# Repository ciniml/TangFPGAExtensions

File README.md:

# Extension boards for Tang series FPGA boards.

## 概要

Sipeedが製造・販売している、Tang Nano 9K, Tang Nano 20K およびTang Primer 20K向けのベースボードおよび拡張基板の設計データです。

## 内容

### 対象ボード

| 名前            | 略称  | 説明                    | 購入先ページ                                              |
| :-------------- | :---- | :---------------------- | :-------------------------------------------------------- |
| Tang Nano 9K    | TN9K  | GW1NR-LV9搭載のボード。 | [秋月電子](https://akizukidenshi.com/catalog/g/gM-17448/) |
| Tang Primer 20K | TN20K | GW2A-LV18PG256          | [秋月電子](https://akizukidenshi.com/catalog/g/gM-17540/) |

### 基板一覧

| 名前                                                                        | 対象ボード | 説明                                            | KiCadプロジェクト                                                                  | リビジョン |
| :-------------------------------------------------------------------------- | :--------- | :---------------------------------------------- | :--------------------------------------------------------------------------------- | ---------- |
| [Tang Nano 9K Pmod Base Board](./README_TangNano_PmodBase.md)               | TN9K       | Tang Nano 9K用のPmod接続用ベースボード          | [TangNano_PmodBase.kicad_pro](./TangNano_PmodBase.kicad_pro)                       | Rev. B     |
| [Tang Primer 20K Pmod Extender ](./README_TangPrimer_PmodExtender.md)       | TP20K      | Tang Primer 20K用のPmod接続用拡張基板           | [TangPrimer_PmodExtender.kicad_pro](./TangPrimer_PmodExtender.kicad_pro)           | Rev. B     |
| [Pmod Debug Board](./README_Pmod_Debug.md)                                  | TN9K,TP20K | Pmodのデバッグ用中継基板                        | [Pmod_Debug.kicad_pro](./Pmod_Debug.kicad_pro)                                     | Rev. A     |
| Pmod HUB75 Connector Board                                                  | TN9K,TP20K | HUB75 LED Matrix接続用Pmod基板                  | [Pmod_HUB75.kicad_pro](./Pmod_HUB75.kicad_pro)                                     | Rev. A     |
| Pmod LED Board                                                              | TN9K,TP20K | Pmodのデバッグ用LED基板                         | [Pmod_LED.kicad_pro](./Pmod_LED.kicad_pro)                                         | Rev. A     |
| [Pmod Matrix LED](./README_Pmod_MatrixLED.md)                               | TN9K,TP20K | 8x8単色LEDマトリクスPmod基板                    | [Pmod_MatrixLED.kicad_pro](./Pmod_MatrixLED.kicad_pro)                             | Rev. B     |
| [Pmod MultiSegment (Single Port)](./README_Pmod_MultiSegment_SinglePort.md) | TN9K,TP20K | 6桁7+1セグメントLED Pmod基板 (シングルポート版) | [Pmod_MultiSegment_SinglePort.kicad_pro](./Pmod_MultiSegment_SinglePort.kicad_pro) | Rev. A     |
| [Pmod Adapter Ethernet](./README_Pmod_Adapter_Ethernet.md) | TN9K,TP20K | LAN8720 Ethernet PHYボード用 Pmod アダプタ | [Pmod_Adapter_Ethernet.kicad_pro](./Pmod_Adapter_Ethernet.kicad_pro) | Rev. A     |

## ライセンス

<br />この 作品 は <a rel="license" href="http://creativecommons.org/licenses/by/4.0/">クリエイティブ・コモンズ 表示 4.0 国際 ライセンス</a>の下に提供されています。

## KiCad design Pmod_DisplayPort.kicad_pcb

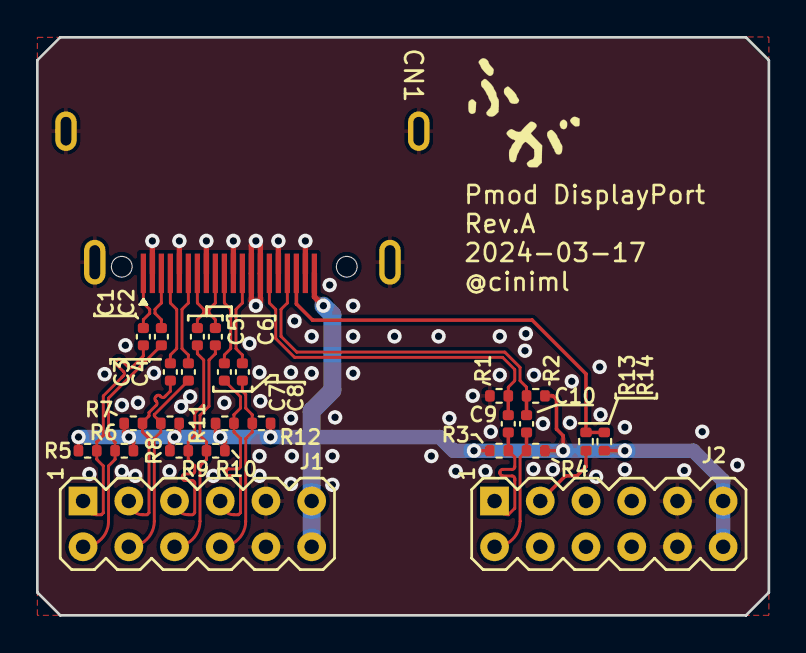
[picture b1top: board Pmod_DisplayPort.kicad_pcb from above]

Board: 2 copper layers, 40.6 x 32.1 mm, 28 parts (0 on the bottom side), 24 nets.

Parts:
C1, C2, C3, C4, C5, C6, C7, C8, C9, C10: 100n; C_0402_1005Metric
CN1: DisplayPort_DP-GD-120PWB
J1, J2: Conn_02x06_Top_Bottom; Conn_Pmod_Spec_B_Thin
LOGO1: Logo_Open_Hardware_Small; logo
R1, R2, R13: 100k; R_0402_1005Metric
R3, R4, R5, R6, R7, R8, R9, R10, R11, R12: 50; R_0402_1005Metric
R14: 10k; R_0402_1005Metric

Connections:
+3V3: CN1.20 (DP_PWR), J1.6, J1.12, J2.6, J2.12, R2.1, R3.1, R4.1, R5.1, R6.1, R7.1, R8.1, R9.1, R10.1, R11.1, R12.1, R13.1
/AUX_N: C10.2, CN1.17 (AUX_CH_N), R2.2
/AUX_P: C9.2, CN1.15 (AUX_CH_P), R1.2
/HPD: CN1.18 (HOT_PLUG), R13.2, R14.1
/ML0_N: C2.2, CN1.3 (ML_LANE0_N)
/ML0_P: C1.2, CN1.1 (ML_LANE0_P)
/ML1_N: C4.2, CN1.6 (ML_LANE1_N)
/ML1_P: C3.2, CN1.4 (ML_LANE1_P)
/ML2_N: C6.2, CN1.9 (ML_LANE2_N)
/ML2_P: C5.2, CN1.7 (ML_LANE2_P)
/ML3_N: C8.2, CN1.12 (ML_LANE3_N)
/ML3_P: C7.2, CN1.10 (ML_LANE3_P)
/PMOD_AUX_CH_N: C10.1, J2.7, R4.2
/PMOD_AUX_CH_P: C9.1, J2.1, R3.2
/PMOD_L0_N: C2.1, J1.7, R6.2
/PMOD_L0_P: C1.1, J1.1, R5.2
/PMOD_L1_N: C4.1, J1.8, R8.2
/PMOD_L1_P: C3.1, J1.2, R7.2
/PMOD_L2_N: C6.1, J1.9, R10.2
/PMOD_L2_P: C5.1, J1.3, R9.2
/PMOD_L3_N: C8.1, J1.10, R12.2
/PMOD_L3_P: C7.1, J1.4, R11.2
/PMOD_P2_HOT_PLUG: J2.2, R14.2
GND: CN1.2 (GND), CN1.5 (GND), CN1.8 (GND), CN1.11 (GND), CN1.13 (CONFIG1), CN1.14 (CONFIG2), CN1.16 (GND), CN1.19 (Return), CN1.FG, J1.5, J1.11, J2.5, J2.11, R1.1

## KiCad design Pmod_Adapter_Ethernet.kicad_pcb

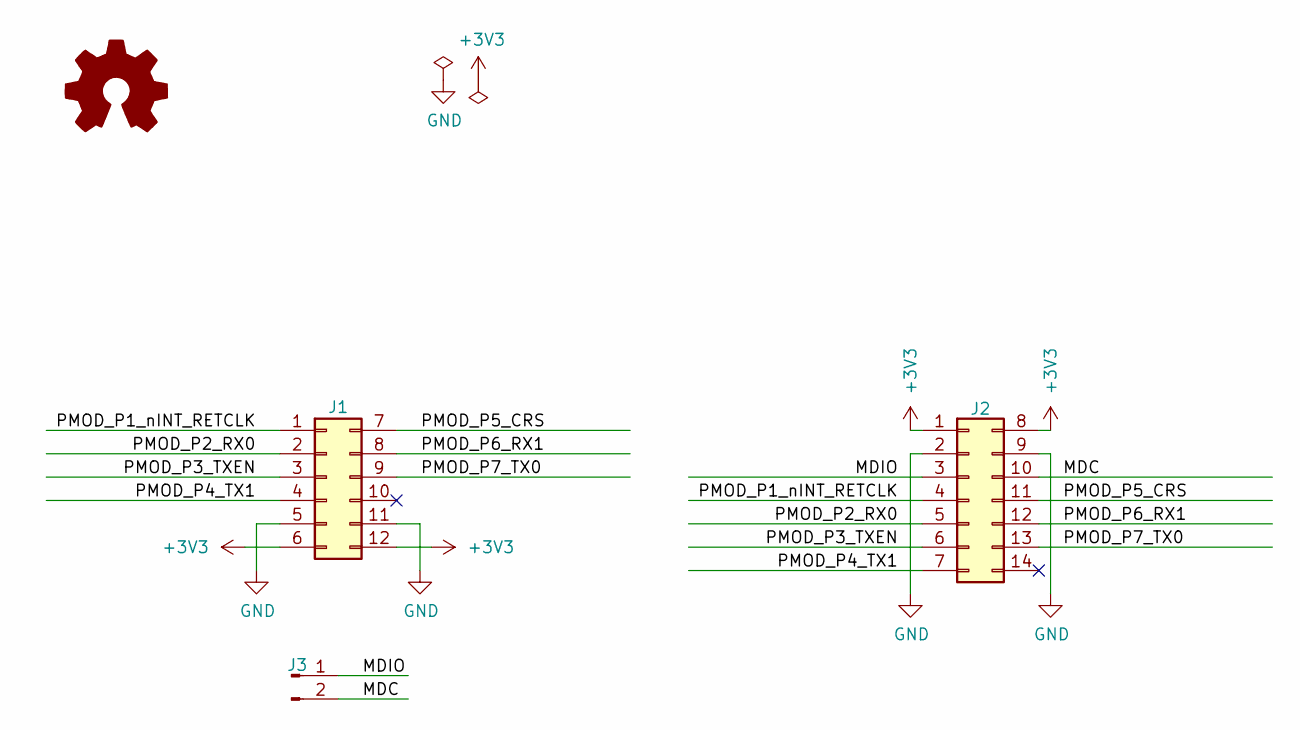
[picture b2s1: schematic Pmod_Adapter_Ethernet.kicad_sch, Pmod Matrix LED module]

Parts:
J1: Conn_02x06_Top_Bottom; Conn_Pmod_Spec_B_Thin
J2: Conn_02x07_Top_Bottom; Conn_WaveShare_Ethernet_Spec_D_Thin
J3: Conn_01x02_Pin; PinHeader_1x02_P2.54mm_Vertical
LOGO1: Logo_Open_Hardware_Small; logo

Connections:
+3V3: J1.6, J1.12, J2.1, J2.8
/MDC: J2.10, J3.2
/MDIO: J2.3, J3.1
/PMOD_P1_nINT_RETCLK: J1.1, J2.4
/PMOD_P2_RX0: J1.2, J2.5
/PMOD_P3_TXEN: J1.3, J2.6
/PMOD_P4_TX1: J1.4, J2.7
/PMOD_P5_CRS: J1.7, J2.11
/PMOD_P6_RX1: J1.8, J2.12
/PMOD_P7_TX0: J1.9, J2.13
GND: J1.5, J1.11, J2.2, J2.9

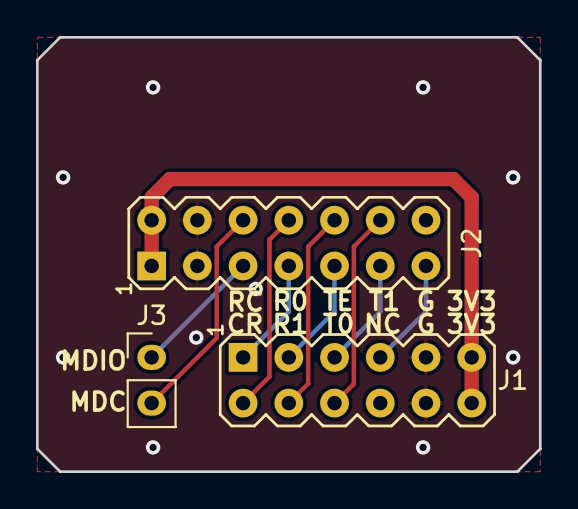
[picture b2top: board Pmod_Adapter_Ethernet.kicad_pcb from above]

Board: 2 copper layers, 27.9 x 24.1 mm, 4 parts (1 on the bottom side), 11 nets.

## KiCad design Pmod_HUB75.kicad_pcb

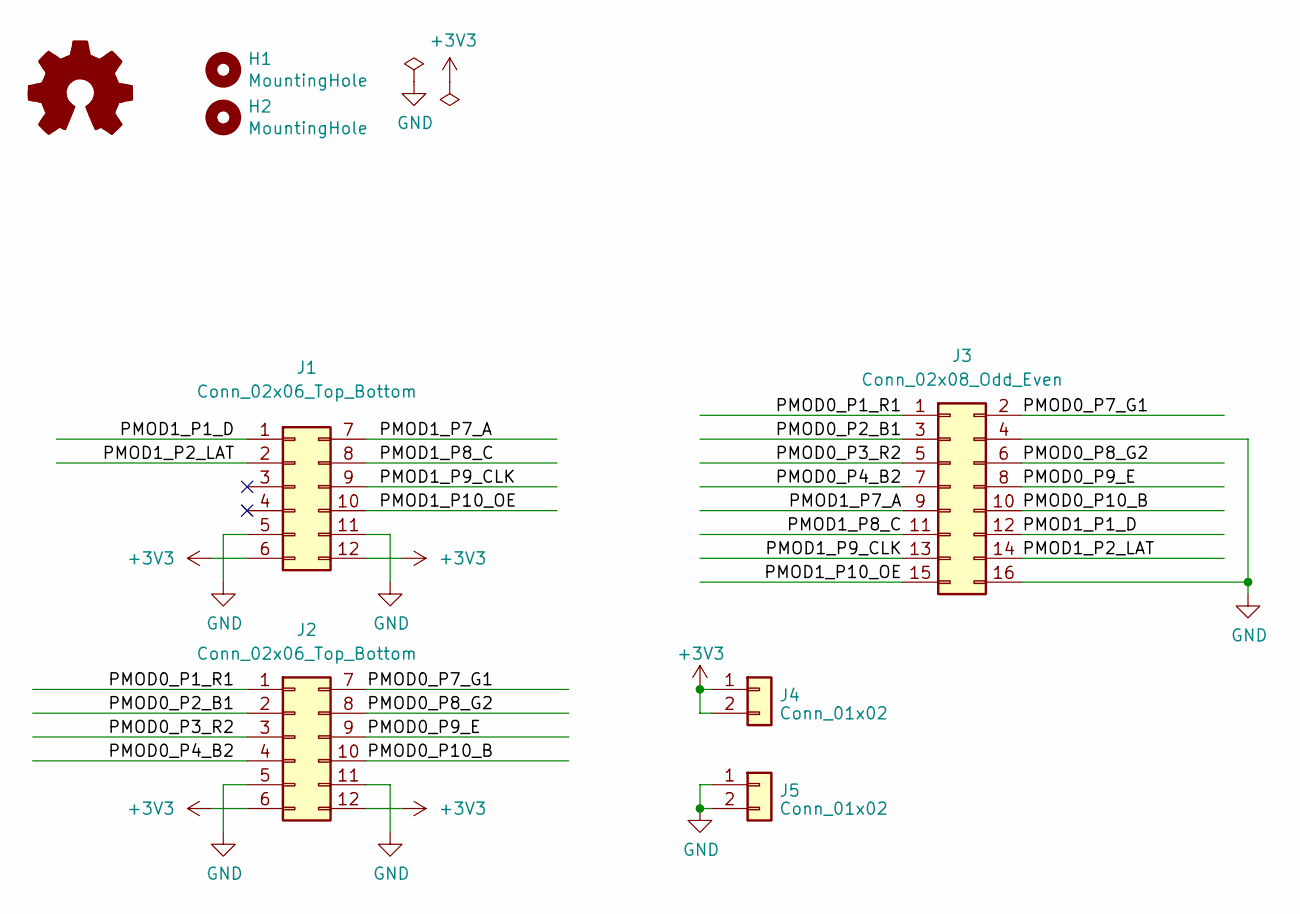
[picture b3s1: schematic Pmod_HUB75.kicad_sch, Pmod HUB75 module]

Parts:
H1, H2: MountingHole; MountingHole_3.2mm_M3_Mask
J1, J2: Conn_02x06_Top_Bottom; Conn_Pmod_Spec_B_Thin
J3: Conn_02x08_Odd_Even; PinHeader_2x08_P2.54mm_Vertical
J4, J5: Conn_01x02; PinHeader_1x02_P2.54mm_Vertical
LOGO1: Logo_Open_Hardware_Small; logo

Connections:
+3V3: J1.6, J1.12, J2.6, J2.12, J4.1, J4.2
/PMOD0_P1_R1: J2.1, J3.1
/PMOD0_P2_B1: J2.2, J3.3
/PMOD0_P3_R2: J2.3, J3.5
/PMOD0_P4_B2: J2.4, J3.7
/PMOD0_P7_G1: J2.7, J3.2
/PMOD0_P8_G2: J2.8, J3.6
/PMOD0_P9_E: J2.9, J3.8
/PMOD0_P10_B: J2.10, J3.10
/PMOD1_P1_D: J1.1, J3.12
/PMOD1_P2_LAT: J1.2, J3.14
/PMOD1_P7_A: J1.7, J3.9
/PMOD1_P8_C: J1.8, J3.11
/PMOD1_P9_CLK: J1.9, J3.13
/PMOD1_P10_OE: J1.10, J3.15
GND: J1.5, J1.11, J2.5, J2.11, J3.4, J3.16, J5.1, J5.2

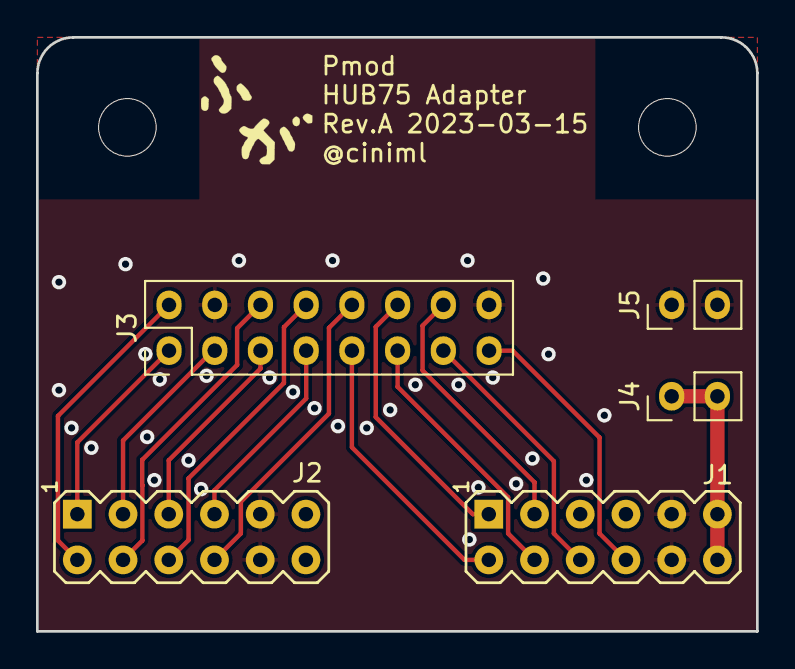
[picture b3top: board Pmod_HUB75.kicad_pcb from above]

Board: 2 copper layers, 40.0 x 33.0 mm, 8 parts (0 on the bottom side), 16 nets.

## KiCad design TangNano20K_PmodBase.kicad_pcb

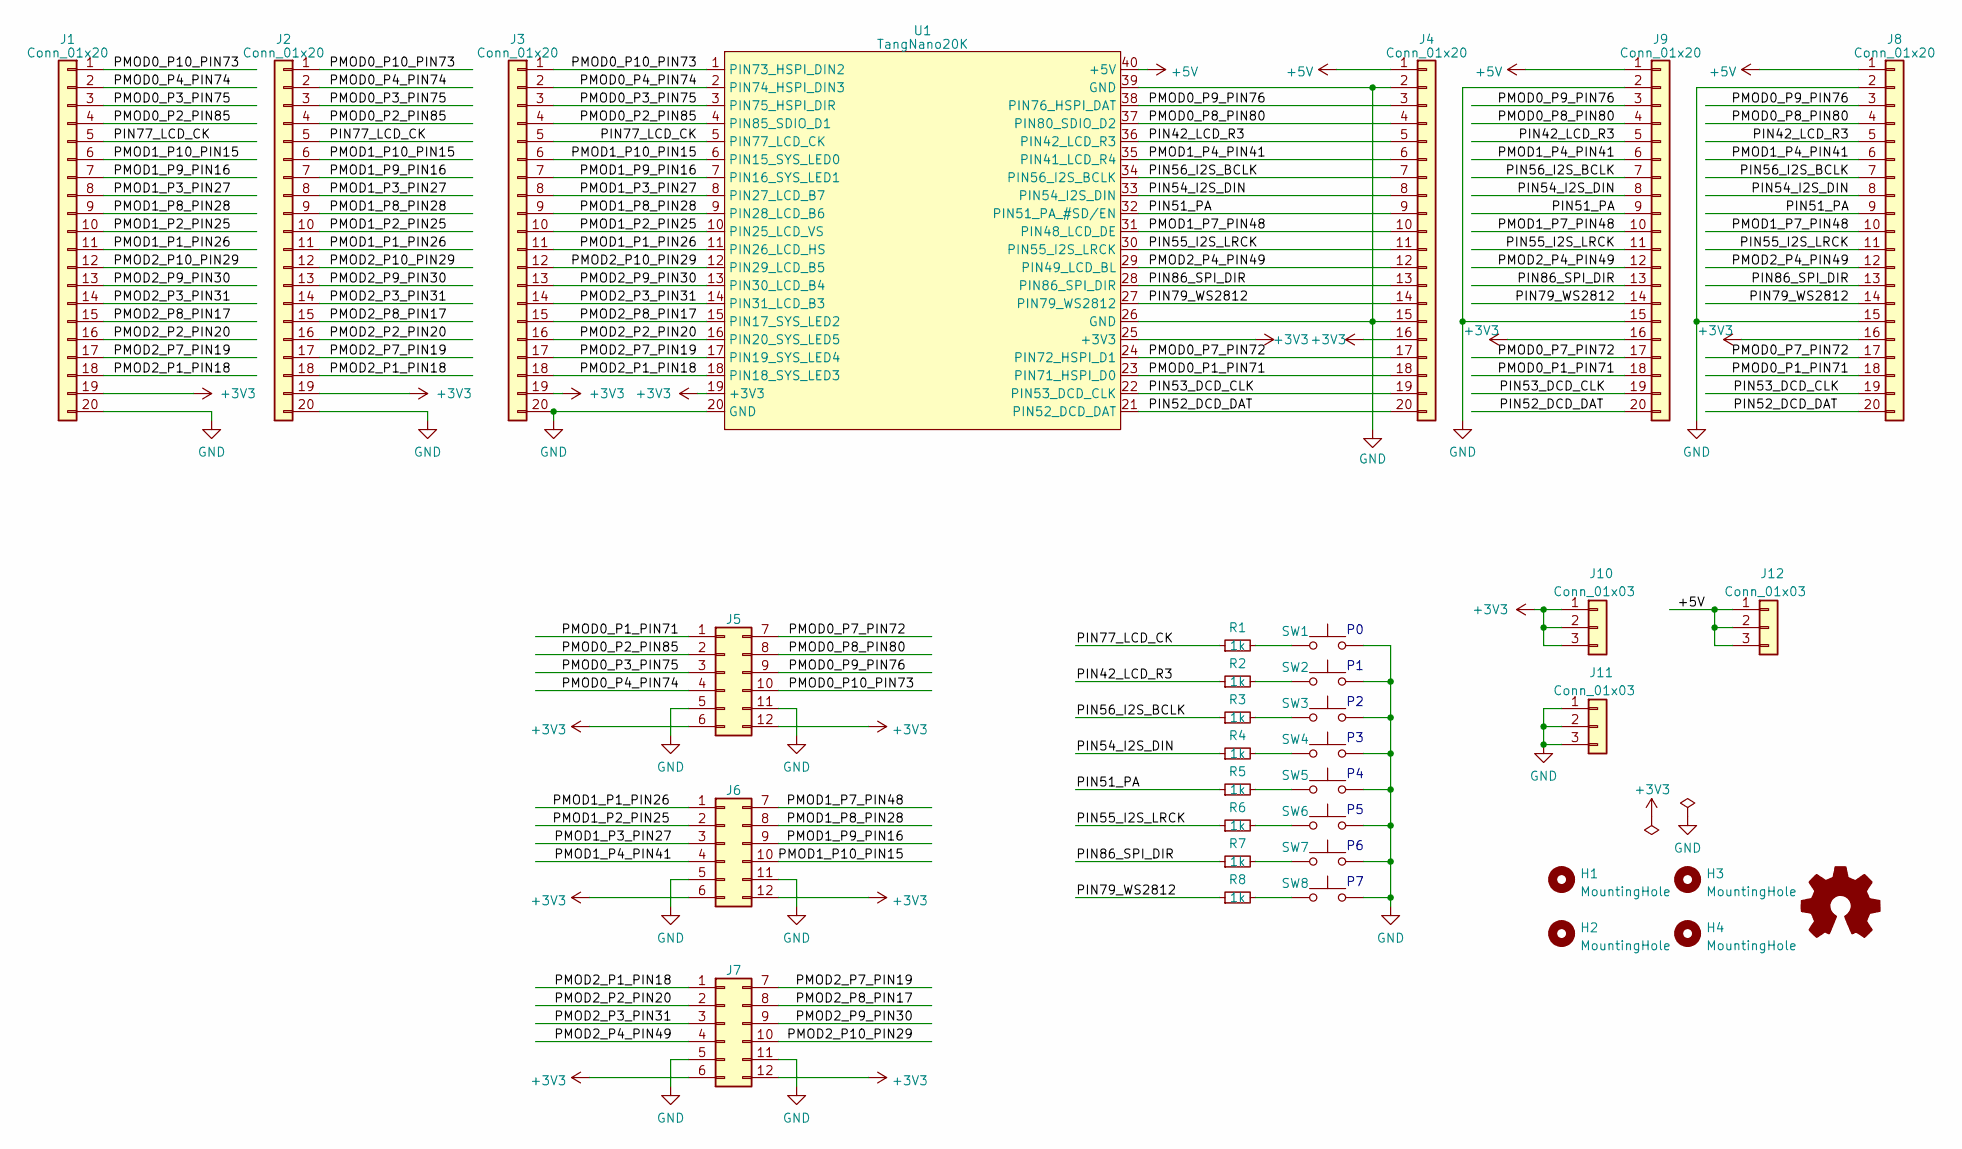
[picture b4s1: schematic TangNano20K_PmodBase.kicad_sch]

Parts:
H1, H2, H3, H4: MountingHole; MountingHole_3.2mm_M3_Mask
J1, J2, J3, J4, J8, J9: Conn_01x20; PinHeader_1x20_P2.54mm_Vertical
J5, J6, J7: Conn_02x06_Top_Bottom; Conn_Pmod_Spec_D_Thin
J10, J11, J12: Conn_01x03; PinHeader_1x03_P2.54mm_Vertical
LOGO1: Logo_Open_Hardware_Small; logo
R1, R2, R3, R4, R5, R6, R7, R8: 1k; R_Axial_DIN0204_L3.6mm_D1.6mm_P5.08mm_Horizontal_with_1608m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
SW1, SW2, SW3, SW4, SW5, SW6, SW7, SW8: SW_Push; TVBP06-BN043XX-B
U1: TangNano20K

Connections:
+3V3: J1.19, J2.19, J3.19, J4.16, J5.6, J5.12, J6.6, J6.12, J7.6, J7.12, J8.16, J9.16, J10.1, J10.2, J10.3, U1.19 (+3V3), U1.25 (+3V3)
+5V: J4.1, J8.1, J9.1, J12.1, J12.2, J12.3, U1.40 (+5V)
/PIN42_LCD_R3: J4.5, J8.5, J9.5, R2.1, U1.36 (PIN42_LCD_R3)
/PIN51_PA: J4.9, J8.9, J9.9, R5.1, U1.32 (PIN51_PA_#SD/EN)
/PIN52_DCD_DAT: J4.20, J8.20, J9.20, U1.21 (PIN52_DCD_DAT)
/PIN53_DCD_CLK: J4.19, J8.19, J9.19, U1.22 (PIN53_DCD_CLK)
/PIN54_I2S_DIN: J4.8, J8.8, J9.8, R4.1, U1.33 (PIN54_I2S_DIN)
/PIN55_I2S_LRCK: J4.11, J8.11, J9.11, R6.1, U1.30 (PIN55_I2S_LRCK)
/PIN56_I2S_BCLK: J4.7, J8.7, J9.7, R3.1, U1.34 (PIN56_I2S_BCLK)
/PIN77_LCD_CK: J1.5, J2.5, J3.5, R1.1, U1.5 (PIN77_LCD_CK)
/PIN79_WS2812: J4.14, J8.14, J9.14, R8.1, U1.27 (PIN79_WS2812)
/PIN86_SPI_DIR: J4.13, J8.13, J9.13, R7.1, U1.28 (PIN86_SPI_DIR)
/PMOD0_P1_PIN71: J4.18, J5.1, J8.18, J9.18, U1.23 (PIN71_HSPI_D0)
/PMOD0_P2_PIN85: J1.4, J2.4, J3.4, J5.2, U1.4 (PIN85_SDIO_D1)
/PMOD0_P3_PIN75: J1.3, J2.3, J3.3, J5.3, U1.3 (PIN75_HSPI_DIR)
/PMOD0_P4_PIN74: J1.2, J2.2, J3.2, J5.4, U1.2 (PIN74_HSPI_DIN3)
/PMOD0_P7_PIN72: J4.17, J5.7, J8.17, J9.17, U1.24 (PIN72_HSPI_D1)
/PMOD0_P8_PIN80: J4.4, J5.8, J8.4, J9.4, U1.37 (PIN80_SDIO_D2)
/PMOD0_P9_PIN76: J4.3, J5.9, J8.3, J9.3, U1.38 (PIN76_HSPI_DAT)
/PMOD0_P10_PIN73: J1.1, J2.1, J3.1, J5.10, U1.1 (PIN73_HSPI_DIN2)
/PMOD1_P1_PIN26: J1.11, J2.11, J3.11, J6.1, U1.11 (PIN26_LCD_HS)
/PMOD1_P2_PIN25: J1.10, J2.10, J3.10, J6.2, U1.10 (PIN25_LCD_VS)
/PMOD1_P3_PIN27: J1.8, J2.8, J3.8, J6.3, U1.8 (PIN27_LCD_B7)
/PMOD1_P4_PIN41: J4.6, J6.4, J8.6, J9.6, U1.35 (PIN41_LCD_R4)
/PMOD1_P7_PIN48: J4.10, J6.7, J8.10, J9.10, U1.31 (PIN48_LCD_DE)
/PMOD1_P8_PIN28: J1.9, J2.9, J3.9, J6.8, U1.9 (PIN28_LCD_B6)
/PMOD1_P9_PIN16: J1.7, J2.7, J3.7, J6.9, U1.7 (PIN16_SYS_LED1)
/PMOD1_P10_PIN15: J1.6, J2.6, J3.6, J6.10, U1.6 (PIN15_SYS_LED0)
/PMOD2_P1_PIN18: J1.18, J2.18, J3.18, J7.1, U1.18 (PIN18_SYS_LED3)
/PMOD2_P2_PIN20: J1.16, J2.16, J3.16, J7.2, U1.16 (PIN20_SYS_LED5)
/PMOD2_P3_PIN31: J1.14, J2.14, J3.14, J7.3, U1.14 (PIN31_LCD_B3)
/PMOD2_P4_PIN49: J4.12, J7.4, J8.12, J9.12, U1.29 (PIN49_LCD_BL)
/PMOD2_P7_PIN19: J1.17, J2.17, J3.17, J7.7, U1.17 (PIN19_SYS_LED4)
/PMOD2_P8_PIN17: J1.15, J2.15, J3.15, J7.8, U1.15 (PIN17_SYS_LED2)
/PMOD2_P9_PIN30: J1.13, J2.13, J3.13, J7.9, U1.13 (PIN30_LCD_B4)
/PMOD2_P10_PIN29: J1.12, J2.12, J3.12, J7.10, U1.12 (PIN29_LCD_B5)
GND: J1.20, J2.20, J3.20, J4.2, J4.15, J5.5, J5.11, J6.5, J6.11, J7.5, J7.11, J8.2, J8.15, J9.2, J9.15, J11.1, J11.2, J11.3, SW1.2, SW2.2, SW3.2, SW4.2, SW5.2, SW6.2, SW7.2, SW8.2, U1.20 (GND), U1.26 (GND), U1.39 (GND)
unnamed: R1.2, SW1.1
unnamed: R2.2, SW2.1
unnamed: R3.2, SW3.1
unnamed: R4.2, SW4.1
unnamed: R5.2, SW5.1
unnamed: R6.2, SW6.1
unnamed: R7.2, SW7.1
unnamed: R8.2, SW8.1

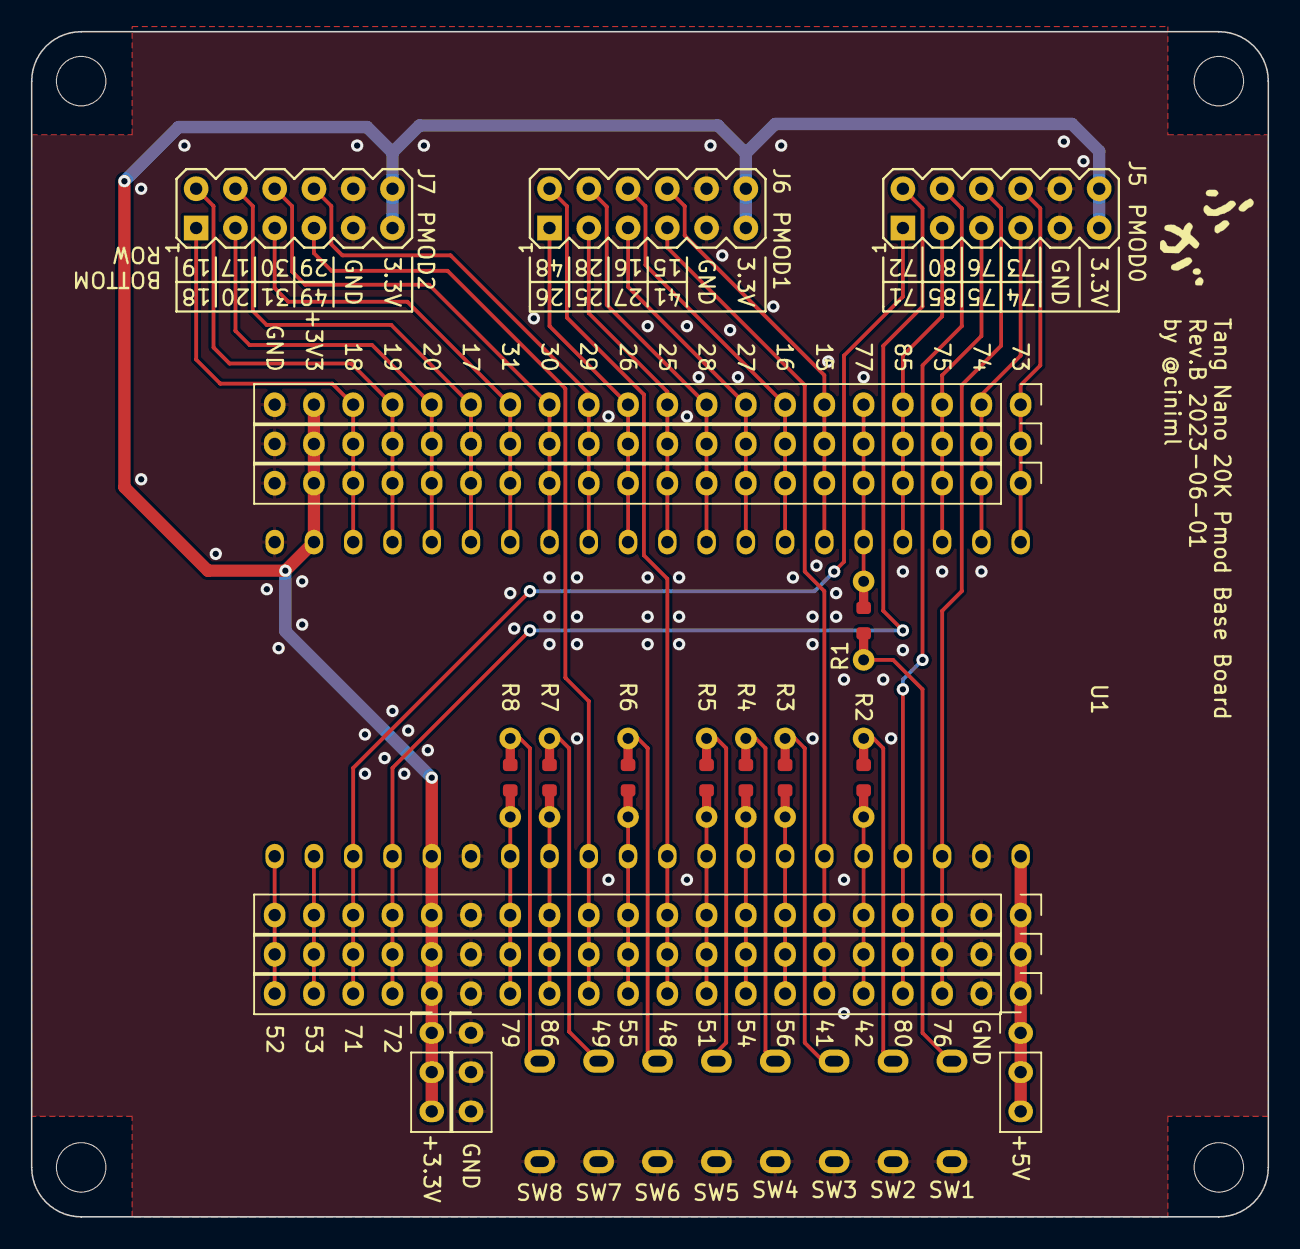
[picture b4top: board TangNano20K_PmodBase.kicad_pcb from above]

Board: 2 copper layers, 80.0 x 76.7 mm, 34 parts (0 on the bottom side), 45 nets.

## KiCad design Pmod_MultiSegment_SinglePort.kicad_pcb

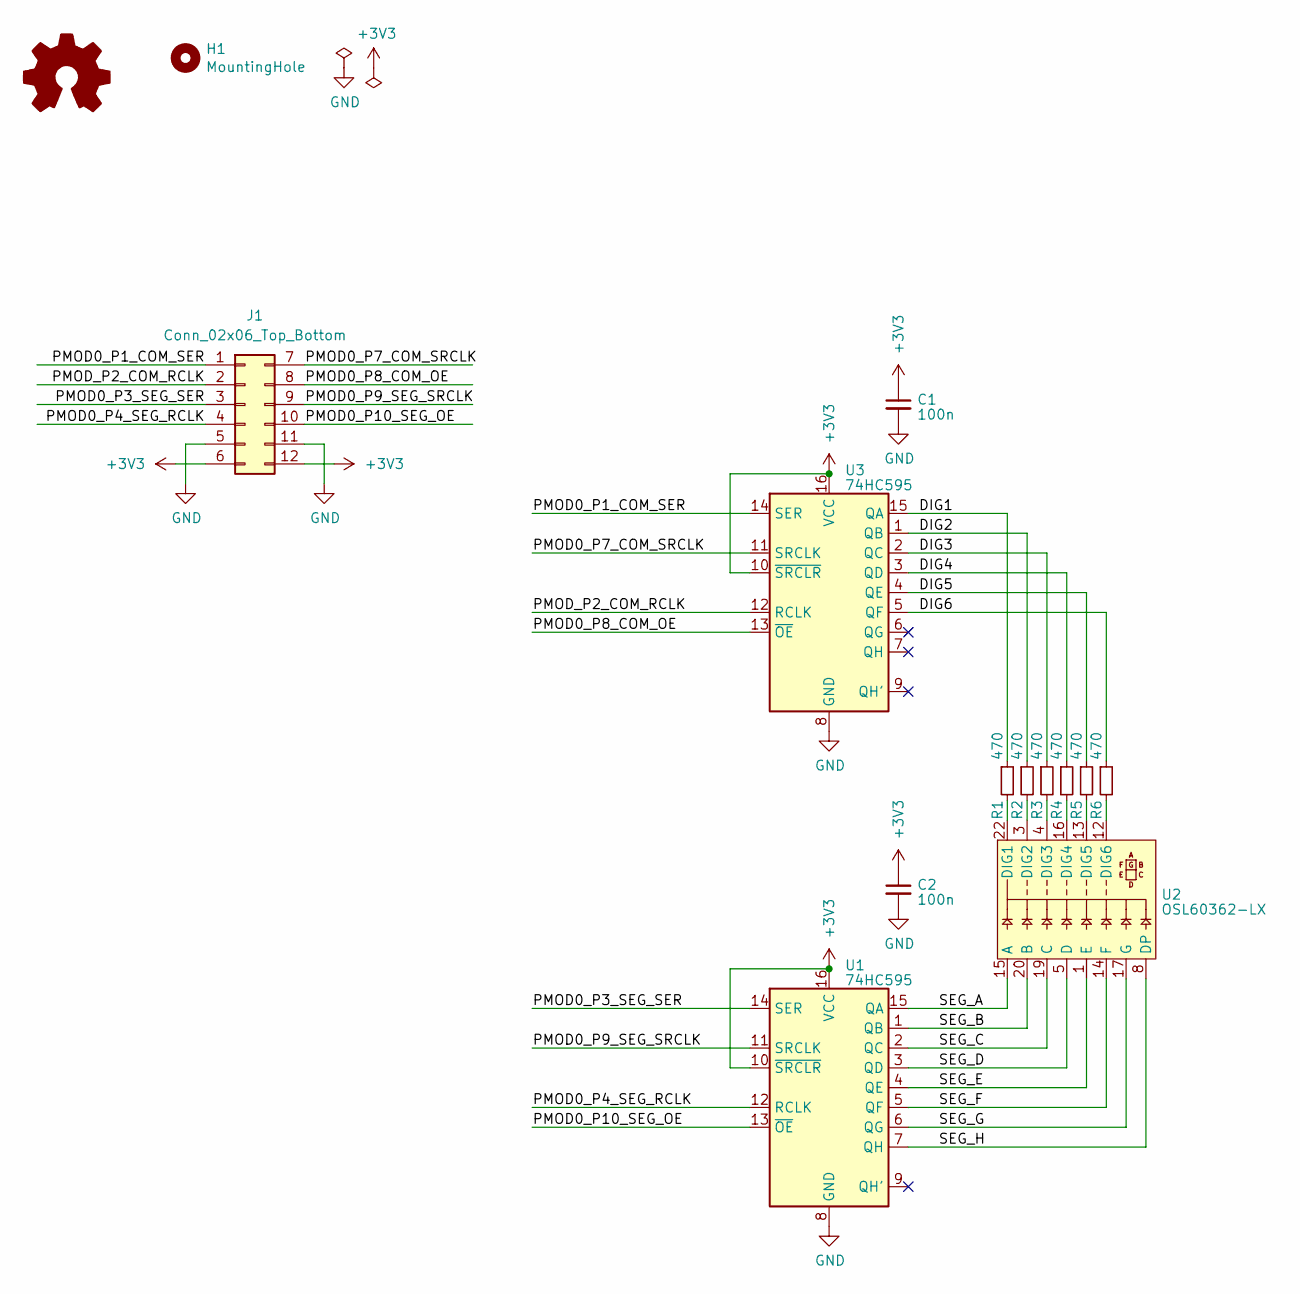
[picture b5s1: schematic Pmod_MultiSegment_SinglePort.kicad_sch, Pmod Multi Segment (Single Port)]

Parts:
C1, C2: 100n; C_0603_1608Metric
H1: MountingHole; MountingHole_3.2mm_M3_Mask
J1: Conn_02x06_Top_Bottom; Conn_Pmod_Spec_B_Thin
LOGO1: Logo_Open_Hardware_Small; logo
R1, R2, R3, R4, R5, R6: 470; R_Axial_DIN0204_L3.6mm_D1.6mm_P5.08mm_Horizontal_with_1608m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
U1, U3: 74HC595; SOIC-16W_5.3x10.2mm_P1.27mm
U2: OSL60362-LX; OSL60362

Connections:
+3V3: C1.1, C2.1, J1.6, J1.12, U1.10 (~SRCLR), U1.16 (VCC), U3.10 (~SRCLR), U3.16 (VCC)
/DIG1: R1.1, U3.15 (QA)
/DIG2: R2.1, U3.1 (QB)
/DIG3: R3.1, U3.2 (QC)
/DIG4: R4.1, U3.3 (QD)
/DIG5: R5.1, U3.4 (QE)
/DIG6: R6.1, U3.5 (QF)
/PMOD0_P1_COM_SER: J1.1, U3.14 (SER)
/PMOD0_P3_SEG_SER: J1.3, U1.14 (SER)
/PMOD0_P4_SEG_RCLK: J1.4, U1.12 (RCLK)
/PMOD0_P7_COM_SRCLK: J1.7, U3.11 (SRCLK)
/PMOD0_P8_COM_OE: J1.8, U3.13 (~OE)
/PMOD0_P9_SEG_SRCLK: J1.9, U1.11 (SRCLK)
/PMOD0_P10_SEG_OE: J1.10, U1.13 (~OE)
/PMOD_P2_COM_RCLK: J1.2, U3.12 (RCLK)
/SEG_A: U1.15 (QA), U2.15 (A)
/SEG_B: U1.1 (QB), U2.20 (B)
/SEG_C: U1.2 (QC), U2.19 (C)
/SEG_D: U1.3 (QD), U2.5 (D)
/SEG_E: U1.4 (QE), U2.1 (E)
/SEG_F: U1.5 (QF), U2.14 (F)
/SEG_G: U1.6 (QG), U2.17 (G)
/SEG_H: U1.7 (QH), U2.8 (DP)
GND: C1.2, C2.2, J1.5, J1.11, U1.8 (GND), U3.8 (GND)
unnamed: R1.2, U2.22 (DIG1)
unnamed: R2.2, U2.3 (DIG2)
unnamed: R3.2, U2.4 (DIG3)
unnamed: R4.2, U2.16 (DIG4)
unnamed: R5.2, U2.13 (DIG5)
unnamed: R6.2, U2.12 (DIG6)

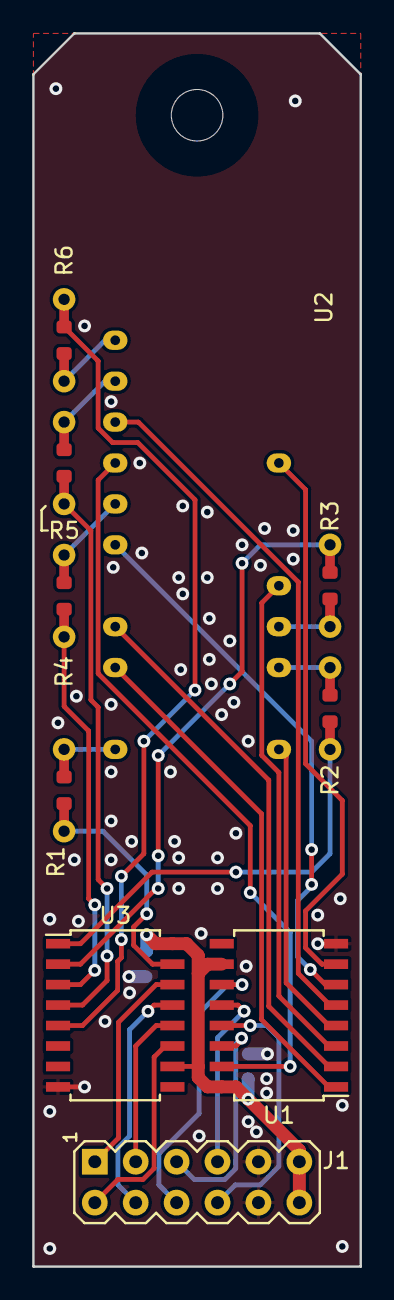
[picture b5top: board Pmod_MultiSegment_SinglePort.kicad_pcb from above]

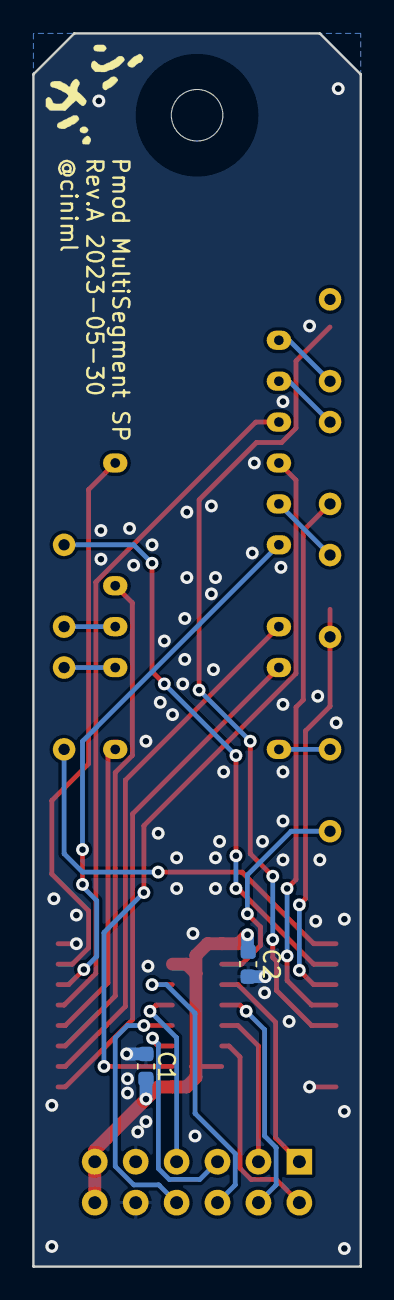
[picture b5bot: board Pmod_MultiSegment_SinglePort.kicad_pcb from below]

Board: 2 copper layers, 20.3 x 76.6 mm, 14 parts (3 on the bottom side), 30 nets.

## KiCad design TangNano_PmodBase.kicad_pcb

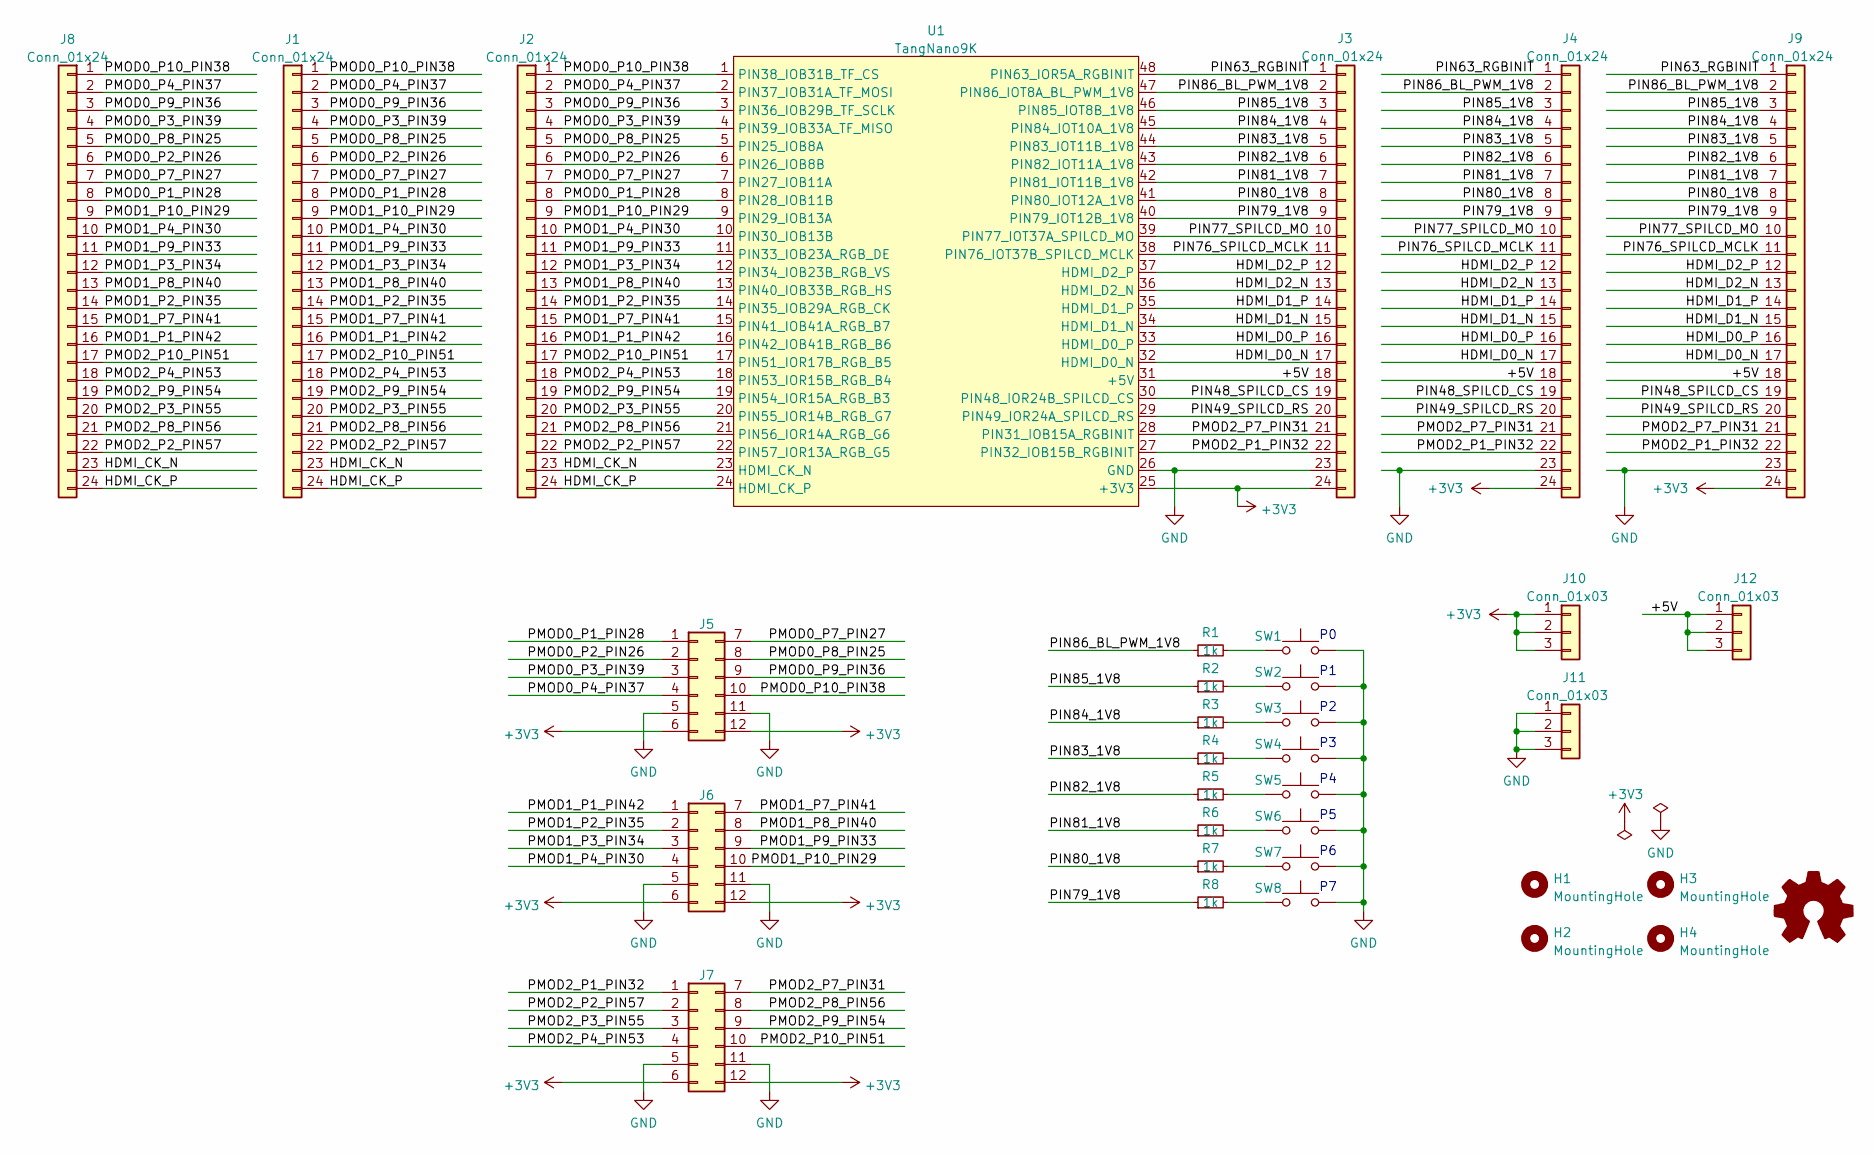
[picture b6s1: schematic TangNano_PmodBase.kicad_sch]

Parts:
H1, H2, H3, H4: MountingHole; MountingHole_3.2mm_M3_Mask
J1, J2, J3, J4, J8, J9: Conn_01x24; PinHeader_1x24_P2.54mm_Vertical
J5, J6, J7: Conn_02x06_Top_Bottom; Conn_Pmod_Spec_D_Thin
J10, J11, J12: Conn_01x03; PinHeader_1x03_P2.54mm_Vertical
LOGO1: Logo_Open_Hardware_Small; logo
R1, R2, R3, R4, R5, R6, R7, R8: 1k; R_Axial_DIN0204_L3.6mm_D1.6mm_P5.08mm_Horizontal_with_1608m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
SW1, SW2, SW3, SW4, SW5, SW6, SW7, SW8: SW_Push; TVBP06-BN043XX-B
U1: TangNano9K

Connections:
+3V3: J3.24, J4.24, J5.6, J5.12, J6.6, J6.12, J7.6, J7.12, J9.24, J10.1, J10.2, J10.3, U1.25 (+3V3)
/+5V: J3.18, J4.18, J9.18, J12.1, J12.2, J12.3, U1.31 (+5V)
/HDMI_CK_N: J1.23, J2.23, J8.23, U1.23 (HDMI_CK_N)
/HDMI_CK_P: J1.24, J2.24, J8.24, U1.24 (HDMI_CK_P)
/HDMI_D0_N: J3.17, J4.17, J9.17, U1.32 (HDMI_D0_N)
/HDMI_D0_P: J3.16, J4.16, J9.16, U1.33 (HDMI_D0_P)
/HDMI_D1_N: J3.15, J4.15, J9.15, U1.34 (HDMI_D1_N)
/HDMI_D1_P: J3.14, J4.14, J9.14, U1.35 (HDMI_D1_P)
/HDMI_D2_N: J3.13, J4.13, J9.13, U1.36 (HDMI_D2_N)
/HDMI_D2_P: J3.12, J4.12, J9.12, U1.37 (HDMI_D2_P)
/PIN48_SPILCD_CS: J3.19, J4.19, J9.19, U1.30 (PIN48_IOR24B_SPILCD_CS)
/PIN49_SPILCD_RS: J3.20, J4.20, J9.20, U1.29 (PIN49_IOR24A_SPILCD_RS)
/PIN63_RGBINIT: J3.1, J4.1, J9.1, U1.48 (PIN63_IOR5A_RGBINIT)
/PIN76_SPILCD_MCLK: J3.11, J4.11, J9.11, U1.38 (PIN76_IOT37B_SPILCD_MCLK)
/PIN77_SPILCD_MO: J3.10, J4.10, J9.10, U1.39 (PIN77_IOT37A_SPILCD_MO)
/PIN79_1V8: J3.9, J4.9, J9.9, R8.1, U1.40 (PIN79_IOT12B_1V8)
/PIN80_1V8: J3.8, J4.8, J9.8, R7.1, U1.41 (PIN80_IOT12A_1V8)
/PIN81_1V8: J3.7, J4.7, J9.7, R6.1, U1.42 (PIN81_IOT11B_1V8)
/PIN82_1V8: J3.6, J4.6, J9.6, R5.1, U1.43 (PIN82_IOT11A_1V8)
/PIN83_1V8: J3.5, J4.5, J9.5, R4.1, U1.44 (PIN83_IOT11B_1V8)
/PIN84_1V8: J3.4, J4.4, J9.4, R3.1, U1.45 (PIN84_IOT10A_1V8)
/PIN85_1V8: J3.3, J4.3, J9.3, R2.1, U1.46 (PIN85_IOT8B_1V8)
/PIN86_BL_PWM_1V8: J3.2, J4.2, J9.2, R1.1, U1.47 (PIN86_IOT8A_BL_PWM_1V8)
/PMOD0_P1_PIN28: J1.8, J2.8, J5.1, J8.8, U1.8 (PIN28_IOB11B)
/PMOD0_P2_PIN26: J1.6, J2.6, J5.2, J8.6, U1.6 (PIN26_IOB8B)
/PMOD0_P3_PIN39: J1.4, J2.4, J5.3, J8.4, U1.4 (PIN39_IOB33A_TF_MISO)
/PMOD0_P4_PIN37: J1.2, J2.2, J5.4, J8.2, U1.2 (PIN37_IOB31A_TF_MOSI)
/PMOD0_P7_PIN27: J1.7, J2.7, J5.7, J8.7, U1.7 (PIN27_IOB11A)
/PMOD0_P8_PIN25: J1.5, J2.5, J5.8, J8.5, U1.5 (PIN25_IOB8A)
/PMOD0_P9_PIN36: J1.3, J2.3, J5.9, J8.3, U1.3 (PIN36_IOB29B_TF_SCLK)
/PMOD0_P10_PIN38: J1.1, J2.1, J5.10, J8.1, U1.1 (PIN38_IOB31B_TF_CS)
/PMOD1_P1_PIN42: J1.16, J2.16, J6.1, J8.16, U1.16 (PIN42_IOB41B_RGB_B6)
/PMOD1_P2_PIN35: J1.14, J2.14, J6.2, J8.14, U1.14 (PIN35_IOB29A_RGB_CK)
/PMOD1_P3_PIN34: J1.12, J2.12, J6.3, J8.12, U1.12 (PIN34_IOB23B_RGB_VS)
/PMOD1_P4_PIN30: J1.10, J2.10, J6.4, J8.10, U1.10 (PIN30_IOB13B)
/PMOD1_P7_PIN41: J1.15, J2.15, J6.7, J8.15, U1.15 (PIN41_IOB41A_RGB_B7)
/PMOD1_P8_PIN40: J1.13, J2.13, J6.8, J8.13, U1.13 (PIN40_IOB33B_RGB_HS)
/PMOD1_P9_PIN33: J1.11, J2.11, J6.9, J8.11, U1.11 (PIN33_IOB23A_RGB_DE)
/PMOD1_P10_PIN29: J1.9, J2.9, J6.10, J8.9, U1.9 (PIN29_IOB13A)
/PMOD2_P1_PIN32: J3.22, J4.22, J7.1, J9.22, U1.27 (PIN32_IOB15B_RGBINIT)
/PMOD2_P2_PIN57: J1.22, J2.22, J7.2, J8.22, U1.22 (PIN57_IOR13A_RGB_G5)
/PMOD2_P3_PIN55: J1.20, J2.20, J7.3, J8.20, U1.20 (PIN55_IOR14B_RGB_G7)
/PMOD2_P4_PIN53: J1.18, J2.18, J7.4, J8.18, U1.18 (PIN53_IOR15B_RGB_B4)
/PMOD2_P7_PIN31: J3.21, J4.21, J7.7, J9.21, U1.28 (PIN31_IOB15A_RGBINIT)
/PMOD2_P8_PIN56: J1.21, J2.21, J7.8, J8.21, U1.21 (PIN56_IOR14A_RGB_G6)
/PMOD2_P9_PIN54: J1.19, J2.19, J7.9, J8.19, U1.19 (PIN54_IOR15A_RGB_B3)
/PMOD2_P10_PIN51: J1.17, J2.17, J7.10, J8.17, U1.17 (PIN51_IOR17B_RGB_B5)
GND: J3.23, J4.23, J5.5, J5.11, J6.5, J6.11, J7.5, J7.11, J9.23, J11.1, J11.2, J11.3, SW1.2, SW2.2, SW3.2, SW4.2, SW5.2, SW6.2, SW7.2, SW8.2, U1.26 (GND)
unnamed: R1.2, SW1.1
unnamed: R2.2, SW2.1
unnamed: R3.2, SW3.1
unnamed: R4.2, SW4.1
unnamed: R5.2, SW5.1
unnamed: R6.2, SW6.1
unnamed: R7.2, SW7.1
unnamed: R8.2, SW8.1

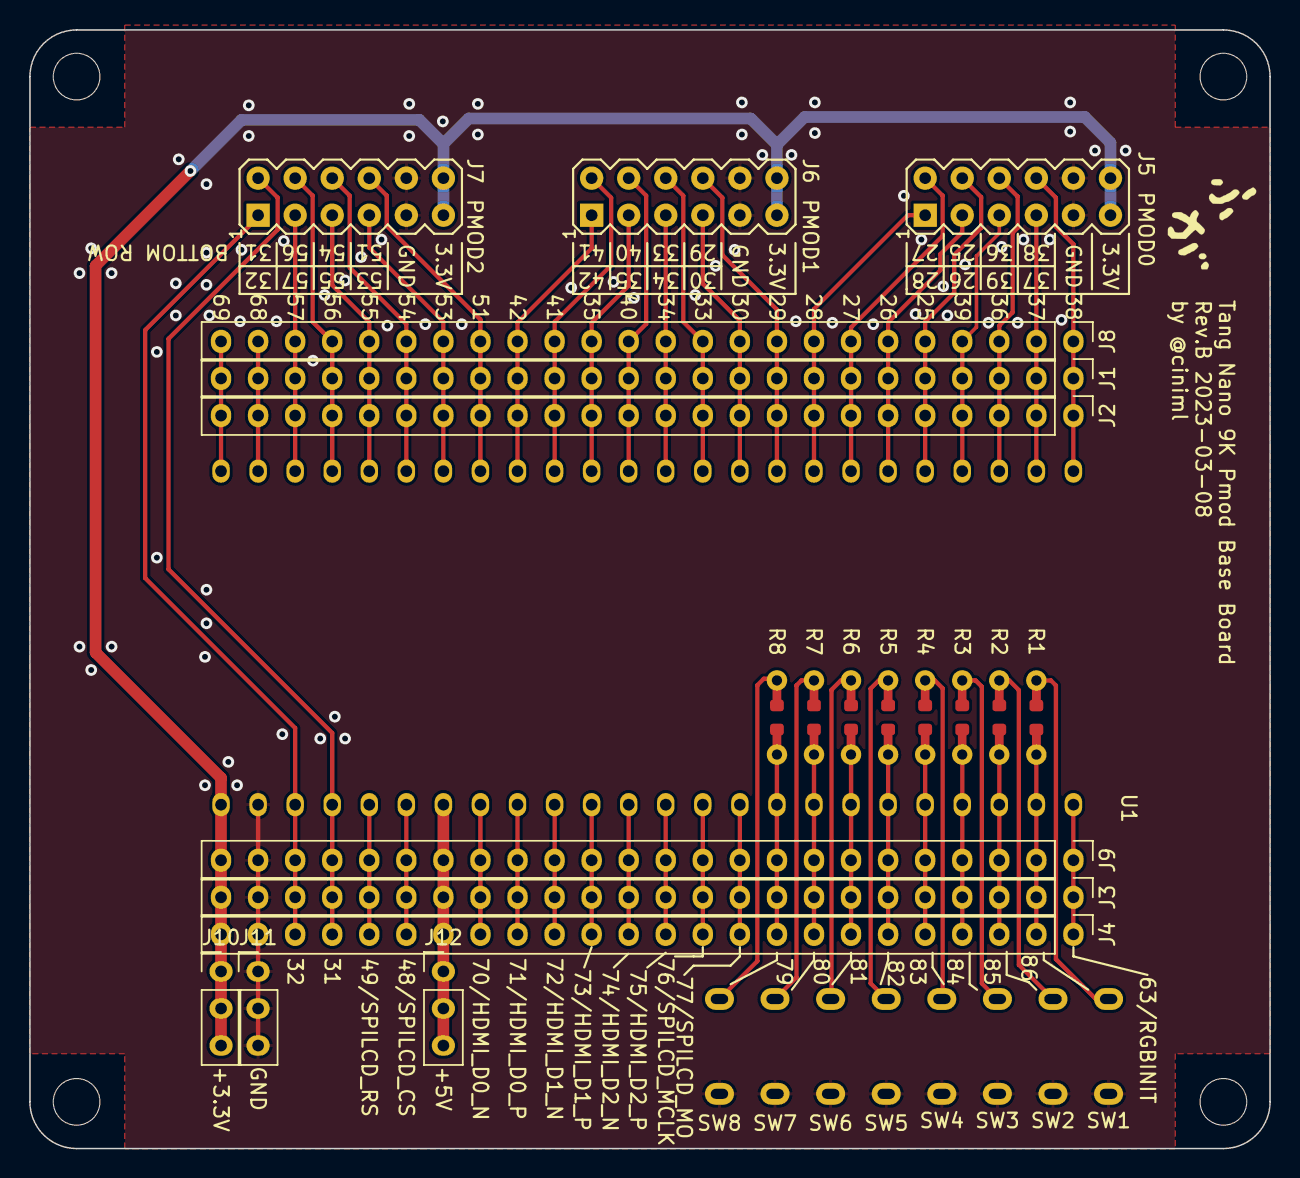
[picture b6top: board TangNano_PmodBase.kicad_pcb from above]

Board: 2 copper layers, 85.0 x 76.7 mm, 34 parts (0 on the bottom side), 56 nets.

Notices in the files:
README.md:
CC BY 4.0
